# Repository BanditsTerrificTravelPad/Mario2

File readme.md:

# Mario 2

PCB to break out a teensy for a 4-panel dance pad

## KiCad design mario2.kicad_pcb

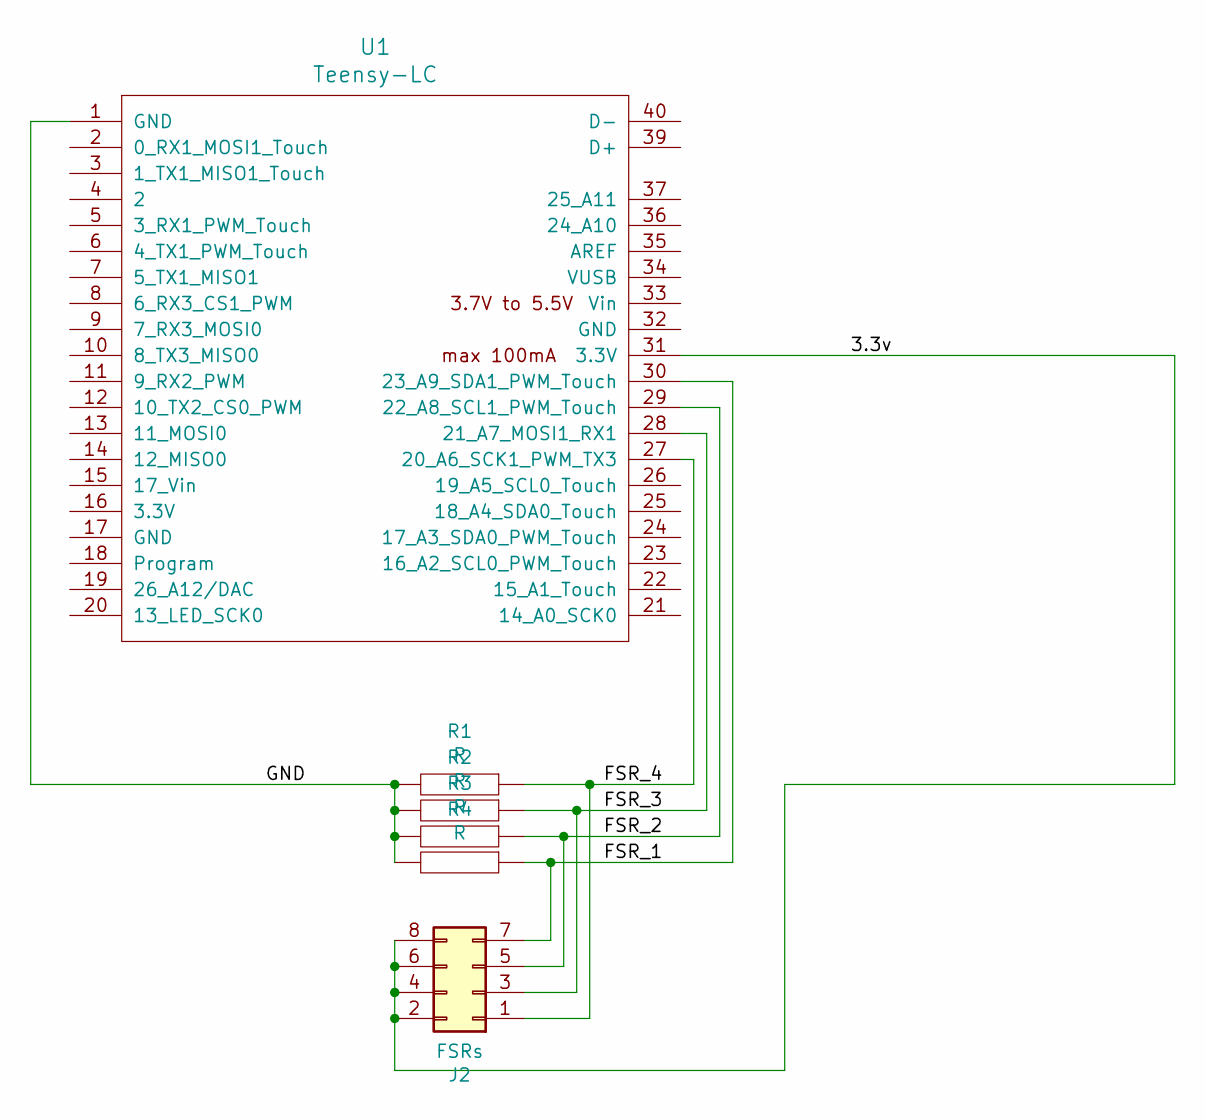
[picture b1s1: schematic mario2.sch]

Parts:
J2: FSRs; PinHeader_2x04_P2.54mm_Horizontal
R1, R2, R3, R4: R; R_Axial_DIN0204_L3.6mm_D1.6mm_P7.62mm_Horizontal
U1: Teensy-LC; Teensy_LC

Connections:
/3.3v: J2.2, J2.4, J2.6, J2.8, U1.31 (3.3V)
/FSR_1: J2.7, R4.1, U1.30 (23_A9_SDA1_PWM_Touch)
/FSR_2: J2.5, R3.1, U1.29 (22_A8_SCL1_PWM_Touch)
/FSR_3: J2.3, R2.1, U1.28 (21_A7_MOSI1_RX1)
/FSR_4: J2.1, R1.1, U1.27 (20_A6_SCK1_PWM_TX3)
/GND: R1.2, R2.2, R3.2, R4.2, U1.1 (GND)

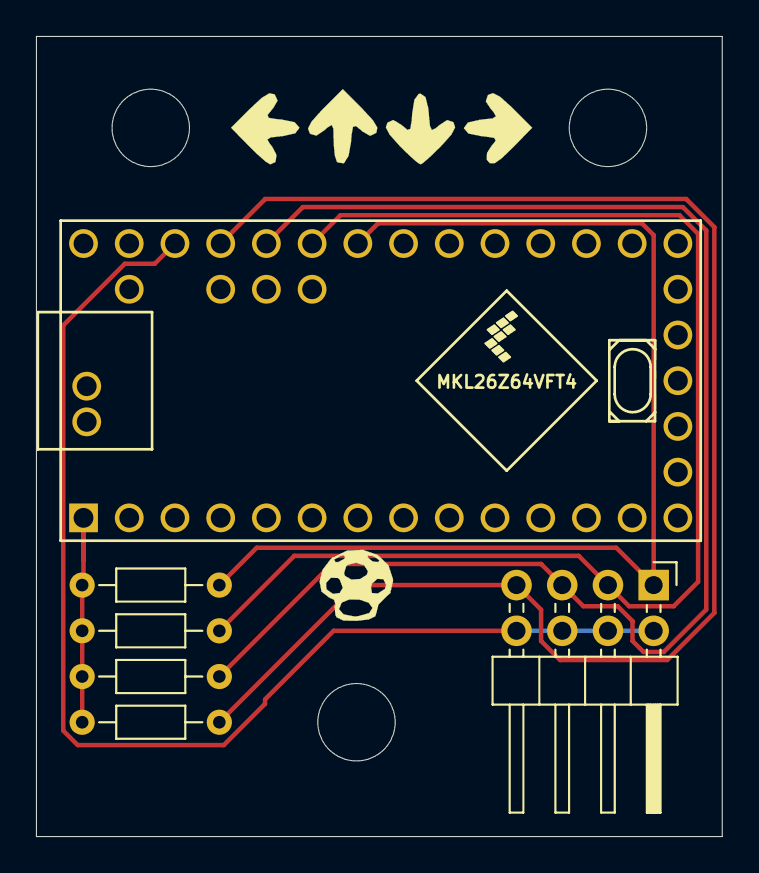
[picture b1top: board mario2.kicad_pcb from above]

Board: 2 copper layers, 38.1 x 44.5 mm, 6 parts (0 on the bottom side), 6 nets.

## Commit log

2021-05-24 Move gerbers to their own folder
2021-05-24 Add needed Teensy symbol libraries
2021-05-24 Clean up schematic wiring
2021-05-24 Add Teensy footprint libraries
2021-05-25 direct solder resistors
2021-05-25 clean up wires
